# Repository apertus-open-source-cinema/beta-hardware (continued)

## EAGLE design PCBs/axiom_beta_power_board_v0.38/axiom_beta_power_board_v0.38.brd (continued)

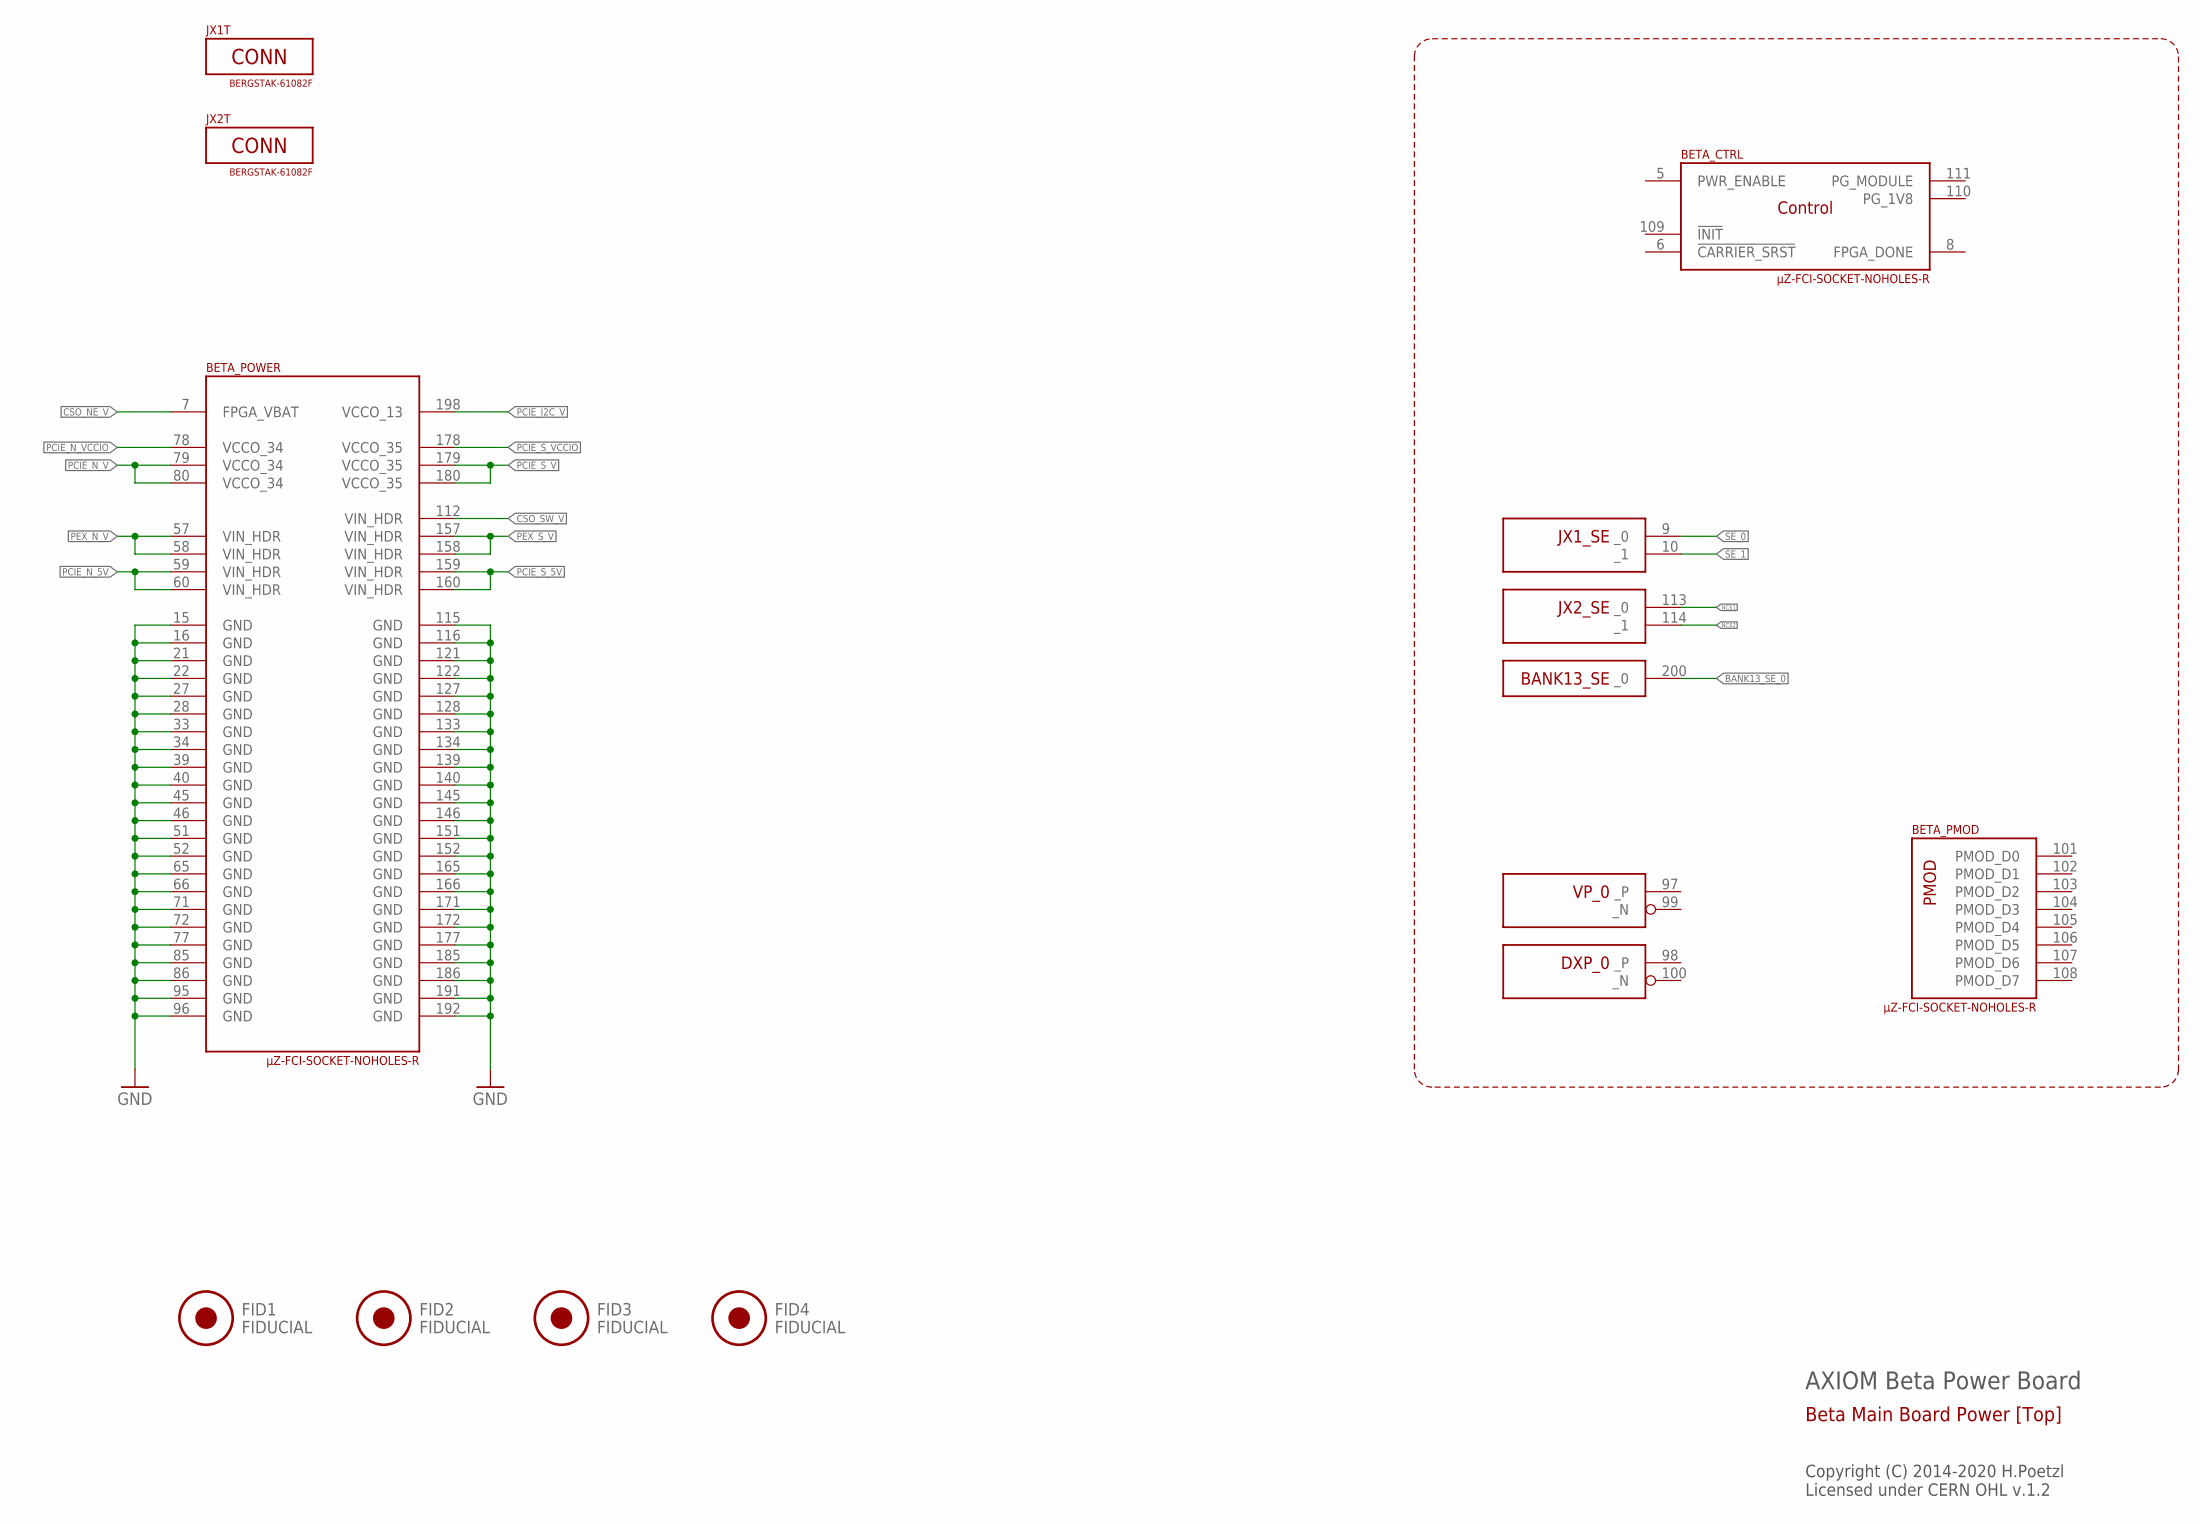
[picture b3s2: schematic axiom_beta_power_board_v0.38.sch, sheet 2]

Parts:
BETA: µZ-FCI-SOCKET-NOHOLES-R; µZ-SOCKET-NOHOLES-R
FID1, FID2, FID3, FID4: FIDUCIAL; FID_ARROW
JX1T, JX2T: BERGSTAK-61082F; 61082-FAKE

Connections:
BANK13_SE_0: BETA.200 (_0); also elsewhere on the board
CSO_NE_V: BETA.7 (FPGA_VBAT); also elsewhere on the board
CSO_SW_V: BETA.112 (VIN_HDR); also elsewhere on the board
GND: BETA.15 (GND), BETA.16 (GND), BETA.21 (GND), BETA.22 (GND), BETA.27 (GND), BETA.28 (GND), BETA.33 (GND), BETA.34 (GND), BETA.39 (GND), BETA.40 (GND), BETA.45 (GND), BETA.46 (GND), BETA.51 (GND), BETA.52 (GND), BETA.65 (GND), BETA.66 (GND), BETA.71 (GND), BETA.72 (GND), BETA.77 (GND), BETA.85 (GND), BETA.86 (GND), BETA.95 (GND), BETA.96 (GND), BETA.115 (GND), BETA.116 (GND), BETA.121 (GND), BETA.122 (GND), BETA.127 (GND), BETA.128 (GND), BETA.133 (GND), BETA.134 (GND), BETA.139 (GND), BETA.140 (GND), BETA.145 (GND), BETA.146 (GND), BETA.151 (GND), BETA.152 (GND), BETA.165 (GND), BETA.166 (GND), BETA.171 (GND), BETA.172 (GND), BETA.177 (GND), BETA.185 (GND), BETA.186 (GND), BETA.191 (GND), BETA.192 (GND); also elsewhere on the board
NC$1: BETA.113 (_0)
NC$2: BETA.114 (_1)
PCIE_I2C_V: BETA.198 (VCCO_13)
PCIE_N_5V: BETA.59 (VIN_HDR), BETA.60 (VIN_HDR)
PCIE_N_V: BETA.79 (VCCO_34), BETA.80 (VCCO_34); also elsewhere on the board
PCIE_N_VCCIO: BETA.78 (VCCO_34)
PCIE_S_5V: BETA.159 (VIN_HDR), BETA.160 (VIN_HDR)
PCIE_S_V: BETA.179 (VCCO_35), BETA.180 (VCCO_35); also elsewhere on the board
PCIE_S_VCCIO: BETA.178 (VCCO_35)
PEX_N_V: BETA.57 (VIN_HDR), BETA.58 (VIN_HDR)
PEX_S_V: BETA.157 (VIN_HDR), BETA.158 (VIN_HDR)
SE_0: BETA.9 (_0); also elsewhere on the board
SE_1: BETA.10 (_1); also elsewhere on the board

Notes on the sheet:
AXIOM Beta Power Board
Copyright (C) 2014-2020 H.Poetzl Licensed under CERN OHL v.1.2
Beta Main Board Power [Top]

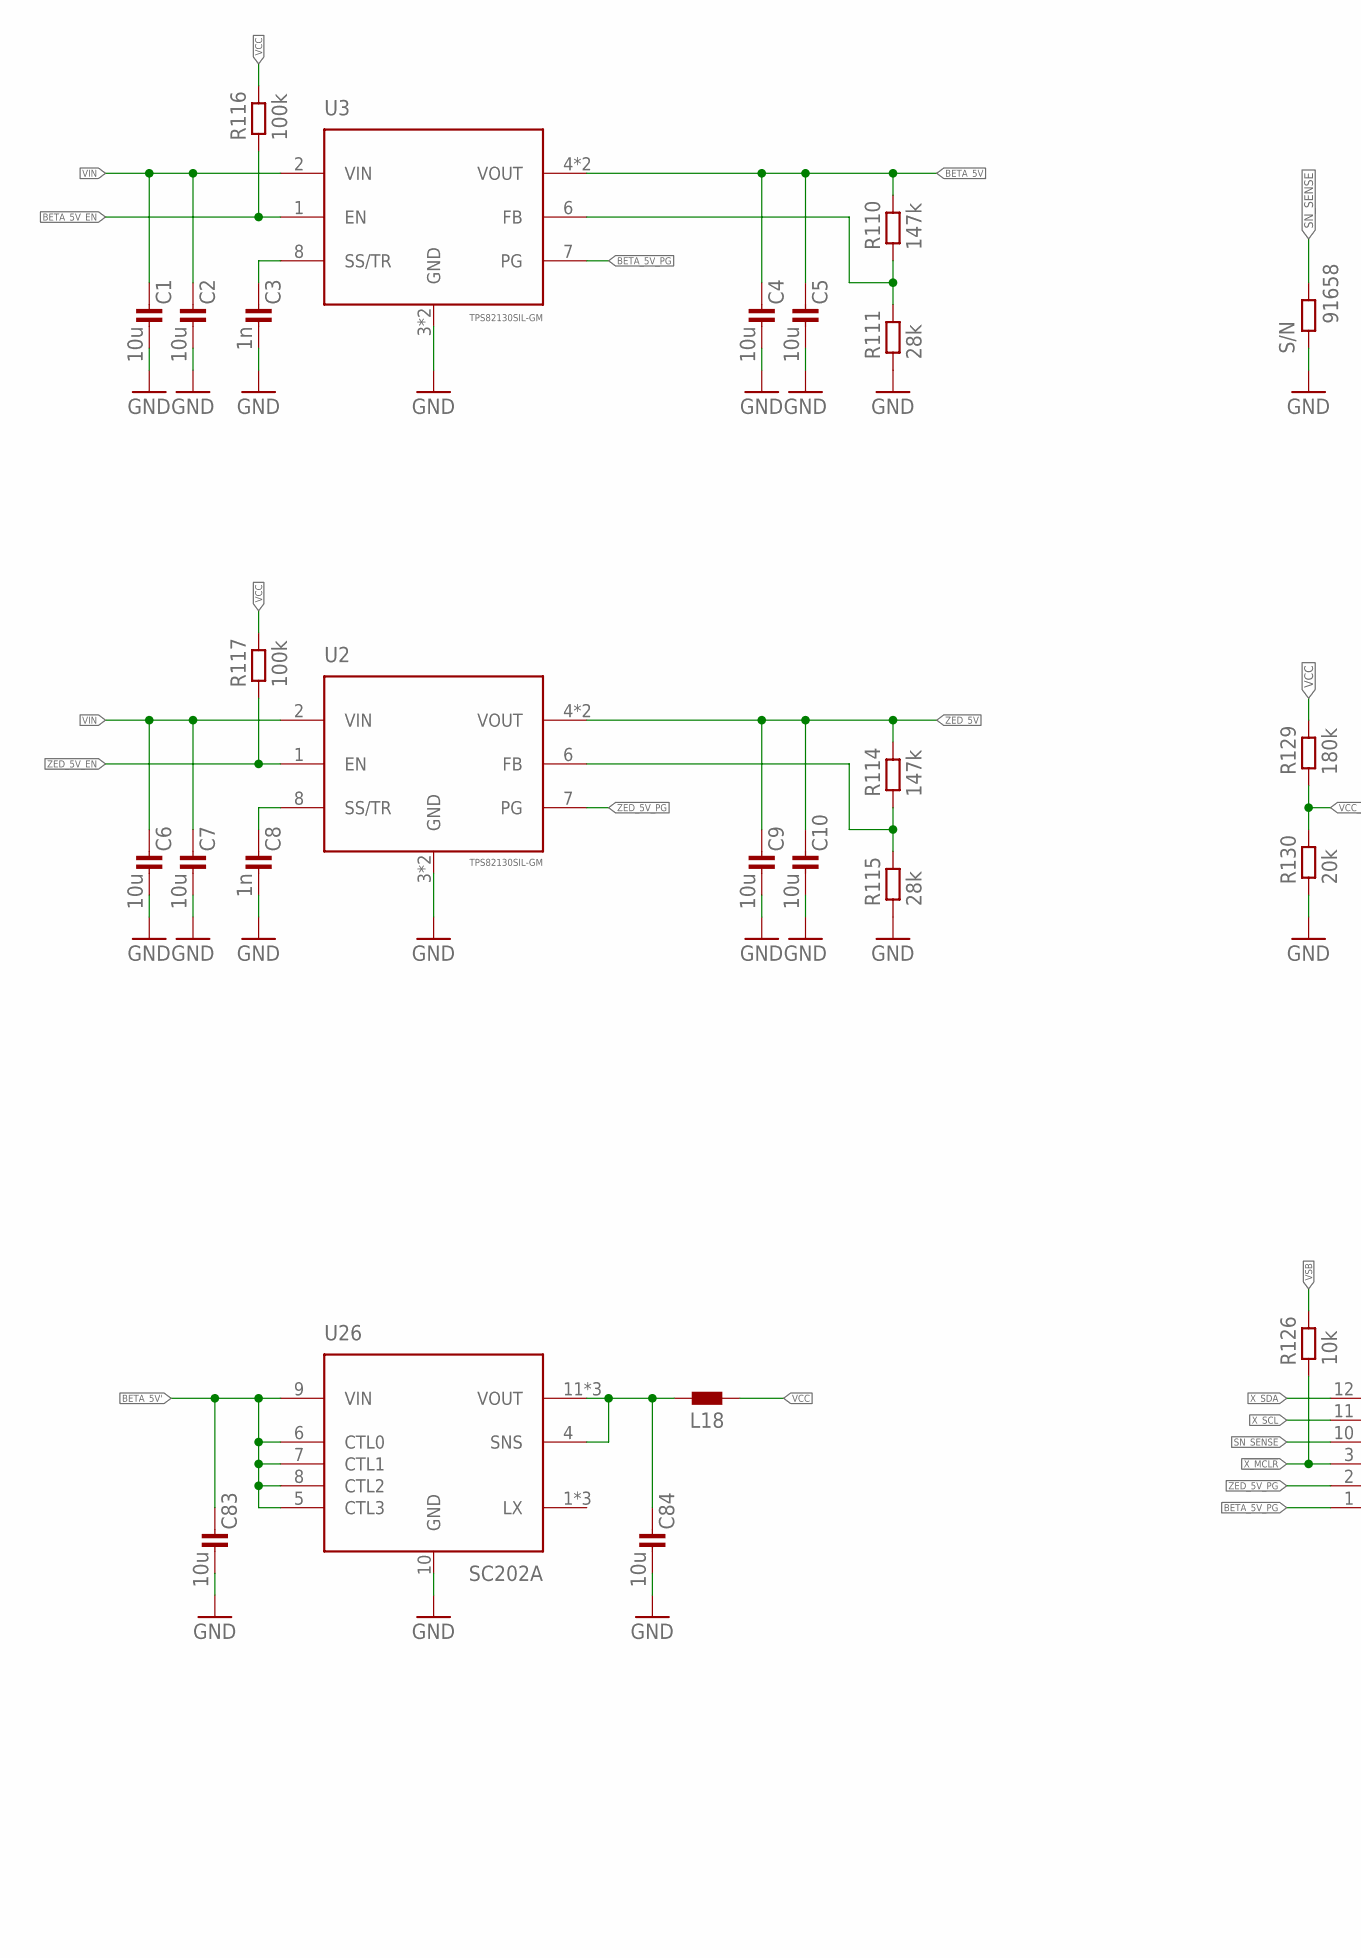
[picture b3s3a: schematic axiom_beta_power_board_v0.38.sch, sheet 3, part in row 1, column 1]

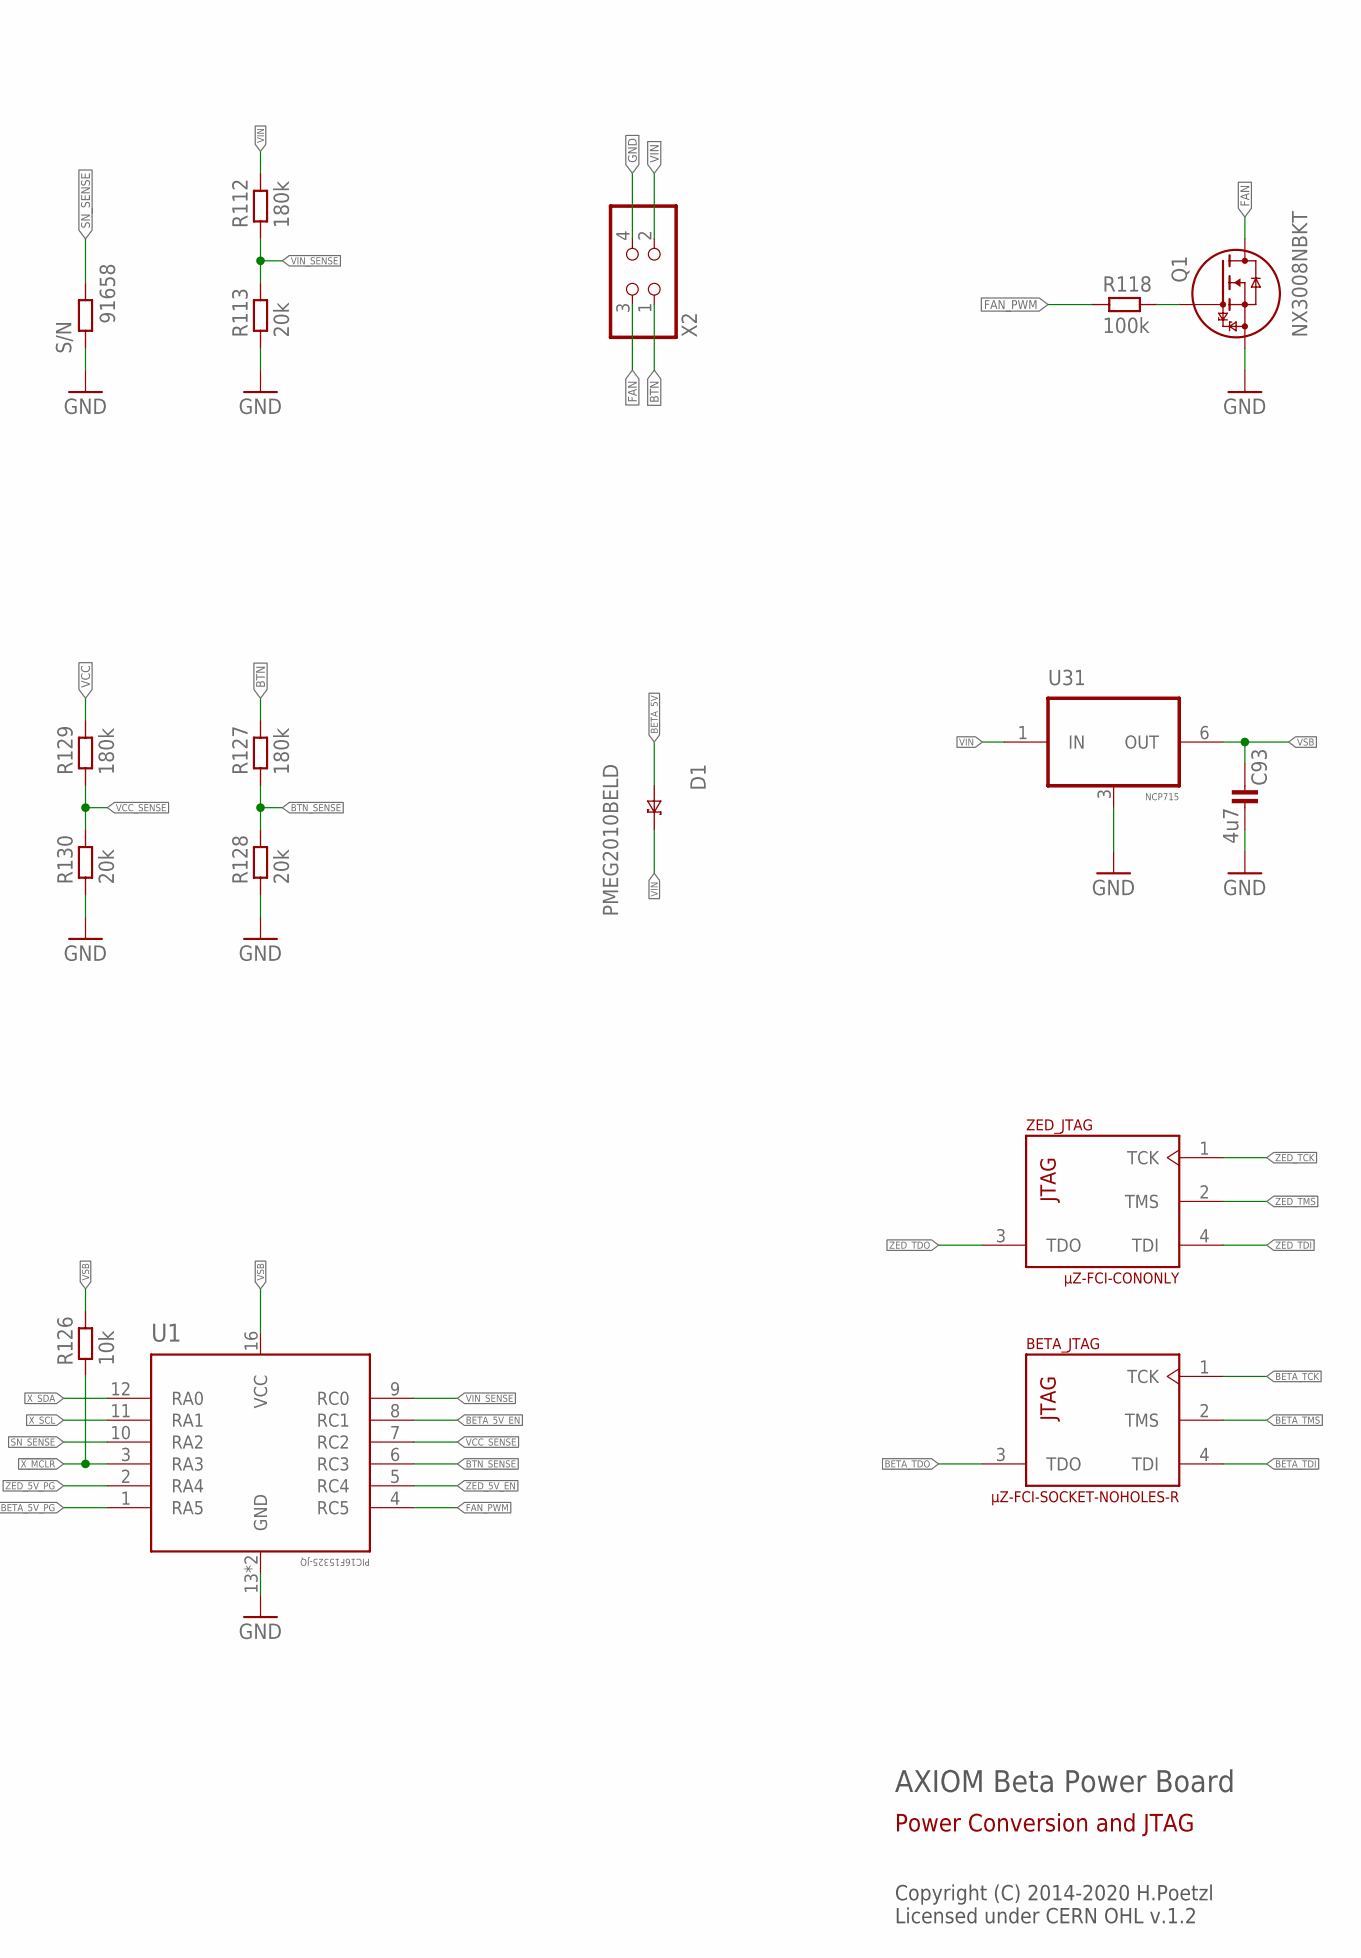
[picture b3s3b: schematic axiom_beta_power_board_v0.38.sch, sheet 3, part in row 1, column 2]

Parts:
BETA: µZ-FCI-SOCKET-NOHOLES-R; µZ-SOCKET-NOHOLES-R
C1, C5, C6, C10: 10u; 0603-B
C2, C4, C7, C9: 10u; 1206-C
C3, C8: 1n; 0402-C
C83, C84: 10u; 0603-C
C93: 4u7; 0402-B
D1: PMEG2010BELD; DFN1006D-2
L18: L0603-C; 0603-C
Q1: NX3008NBKT; SOT416
R110, R114: 147k; 0402-C
R111, R115: 28k; 0402-C
R112: 180k; 0402-B
R113: 20k; 0402-B
R116, R117: 100k; 0402-B
R118: 100k; 0402-C
R126: 10k; 0402-B
R127, R129: 180k; 0402-C
R128, R130: 20k; 0402-C
S/N: 91658; 3X2MM
U1: PIC16F15325-JQ; UQFN65P400X400X100-17N
U2, U3: TPS82130SIL-GM; SIL0008D-GM
U26: SC202A; MLPQ-13
U31: NCP715; DFN150X150X50-6N
X2: PINHD-2X02_2.54-90°; 2X02/90
ZED: µZ-FCI-CONONLY; µZ-CONONLY

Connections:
!X_MCLR: R126.2, U1.3 (RA3); also elsewhere on the board
BETA_5V: C4.1, C5.1, D1.A, R110.1, U3.4 (VOUT), U3.5 (VOUT); also elsewhere on the board
BETA_5V': C83.1, U26.5 (CTL3), U26.6 (CTL0), U26.7 (CTL1), U26.8 (CTL2), U26.9 (VIN); also elsewhere on the board
BETA_5V_EN: R116.2, U1.8 (RC1), U3.1 (EN)
BETA_5V_PG: U1.1 (RA5), U3.7 (PG)
BETA_TCK: BETA.1 (TCK)
BETA_TDI: BETA.4 (TDI)
BETA_TDO: BETA.3 (TDO)
BETA_TMS: BETA.2 (TMS)
BTN: R127.1, X2.1
BTN_SENSE: R127.2, R128.1, U1.6 (RC3)
FAN: Q1.3 (D), X2.3
FAN_PWM: R118.2, U1.4 (RC5)
GND: C1.2, C2.2, C3.2, C4.2, C5.2, C6.2, C7.2, C8.2, C9.2, C10.2, C83.2, C84.2, C93.2, Q1.2 (S), R111.2, R113.2, R115.2, R128.2, R130.2, S/N.1, U1.13 (GND), U1.EP (GND), U2.3 (GND), U2.EPAD (GND), U3.3 (GND), U3.EPAD (GND), U26.10 (GND), U31.3 (GND), X2.4; also elsewhere on the board
unnamed: C8.1, U2.8 (SS/TR)
unnamed: C3.1, U3.8 (SS/TR)
unnamed: Q1.1 (G), R118.1
unnamed: R110.2, R111.1, U3.6 (FB)
unnamed: R114.2, R115.1, U2.6 (FB)
REGOUT: C84.1, L18.1, U26.4 (SNS), U26.11 (VOUT), U26.12 (VOUT), U26.13 (VOUT)
SN_SENSE: S/N.2, U1.10 (RA2)
VCC: L18.2, R116.1, R117.1, R129.1; also elsewhere on the board
VCC_SENSE: R129.2, R130.1, U1.7 (RC2)
VIN: C1.1, C2.1, C6.1, C7.1, D1.C (K), R112.1, U2.2 (VIN), U3.2 (VIN), U31.1 (IN), X2.2
VIN_SENSE: R112.2, R113.1, U1.9 (RC0)
VSB: C93.1, R126.1, U1.16 (VCC), U31.6 (OUT); also elsewhere on the board
X_SCL: U1.11 (RA1); also elsewhere on the board
X_SDA: U1.12 (RA0); also elsewhere on the board
ZED_5V: C9.1, C10.1, R114.1, U2.4 (VOUT), U2.5 (VOUT); also elsewhere on the board
ZED_5V_EN: R117.2, U1.5 (RC4), U2.1 (EN)
ZED_5V_PG: U1.2 (RA4), U2.7 (PG)
ZED_TCK: ZED.1 (TCK)
ZED_TDI: ZED.4 (TDI)
ZED_TDO: ZED.3 (TDO)
ZED_TMS: ZED.2 (TMS)

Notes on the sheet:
AXIOM Beta Power Board
Copyright (C) 2014-2020 H.Poetzl Licensed under CERN OHL v.1.2
Power Conversion and JTAG

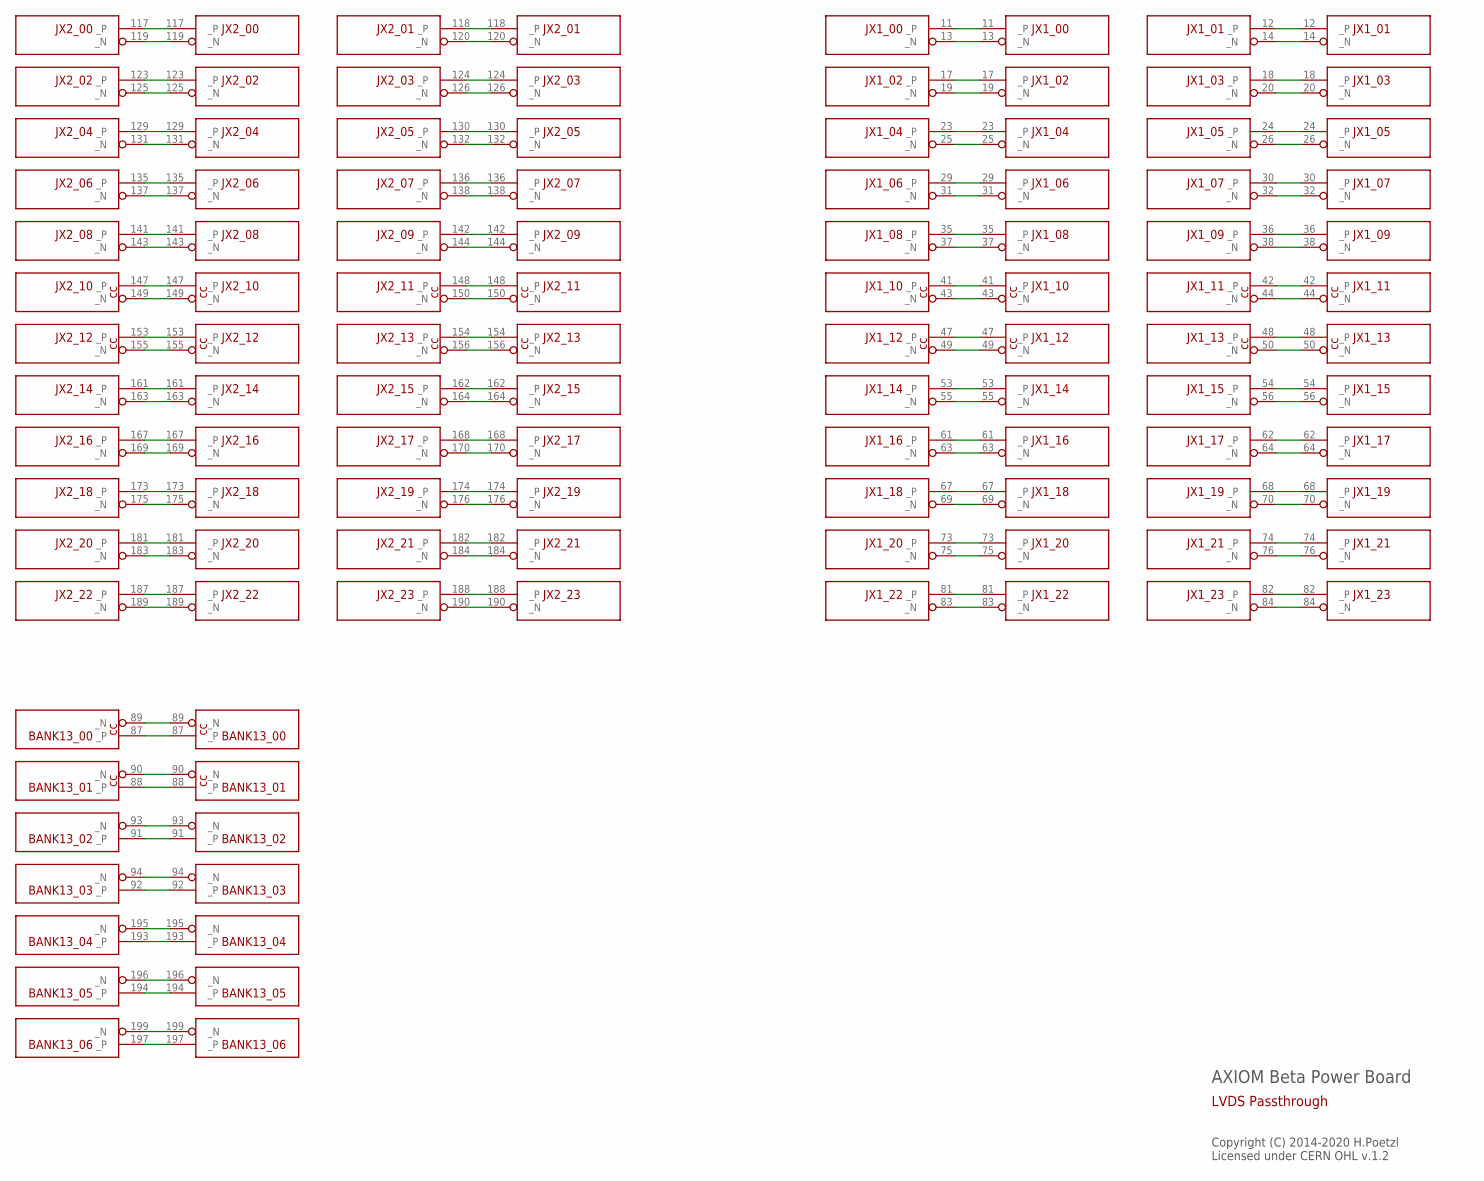
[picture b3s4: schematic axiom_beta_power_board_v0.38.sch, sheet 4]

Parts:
BETA: µZ-FCI-SOCKET-NOHOLES-R; µZ-SOCKET-NOHOLES-R
ZED: µZ-FCI-CONONLY; µZ-CONONLY

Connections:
BANK13_00_N: BETA.89 (_N), ZED.89 (_N)
BANK13_00_P: BETA.87 (_P), ZED.87 (_P)
BANK13_01_N: BETA.90 (_N), ZED.90 (_N)
BANK13_01_P: BETA.88 (_P), ZED.88 (_P)
BANK13_02_N: BETA.93 (_N), ZED.93 (_N)
BANK13_02_P: BETA.91 (_P), ZED.91 (_P)
BANK13_03_N: BETA.94 (_N), ZED.94 (_N)
BANK13_03_P: BETA.92 (_P), ZED.92 (_P)
BANK13_04_N: BETA.195 (_N), ZED.195 (_N)
BANK13_04_P: BETA.193 (_P), ZED.193 (_P)
BANK13_05_N: BETA.196 (_N), ZED.196 (_N)
BANK13_05_P: BETA.194 (_P), ZED.194 (_P)
BANK13_06_N: BETA.199 (_N), ZED.199 (_N)
BANK13_06_P: BETA.197 (_P), ZED.197 (_P)
JX1_00_N: BETA.13 (_N), ZED.13 (_N)
JX1_00_P: BETA.11 (_P), ZED.11 (_P)
JX1_01_N: BETA.14 (_N), ZED.14 (_N)
JX1_01_P: BETA.12 (_P), ZED.12 (_P)
JX1_02_N: BETA.19 (_N), ZED.19 (_N)
JX1_02_P: BETA.17 (_P), ZED.17 (_P)
JX1_03_N: BETA.20 (_N), ZED.20 (_N)
JX1_03_P: BETA.18 (_P), ZED.18 (_P)
JX1_04_N: BETA.25 (_N), ZED.25 (_N)
JX1_04_P: BETA.23 (_P), ZED.23 (_P)
JX1_05_N: BETA.26 (_N), ZED.26 (_N)
JX1_05_P: BETA.24 (_P), ZED.24 (_P)
JX1_06_N: BETA.31 (_N), ZED.31 (_N)
JX1_06_P: BETA.29 (_P), ZED.29 (_P)
JX1_07_N: BETA.32 (_N), ZED.32 (_N)
JX1_07_P: BETA.30 (_P), ZED.30 (_P)
JX1_08_N: BETA.37 (_N), ZED.37 (_N)
JX1_08_P: BETA.35 (_P), ZED.35 (_P)
JX1_09_N: BETA.38 (_N), ZED.38 (_N)
JX1_09_P: BETA.36 (_P), ZED.36 (_P)
JX1_10_N: BETA.43 (_N), ZED.43 (_N)
JX1_10_P: BETA.41 (_P), ZED.41 (_P)
JX1_11_N: BETA.44 (_N), ZED.44 (_N)
JX1_11_P: BETA.42 (_P), ZED.42 (_P)
JX1_12_N: BETA.49 (_N), ZED.49 (_N)
JX1_12_P: BETA.47 (_P), ZED.47 (_P)
JX1_13_N: BETA.50 (_N), ZED.50 (_N)
JX1_13_P: BETA.48 (_P), ZED.48 (_P)
JX1_14_N: BETA.55 (_N), ZED.55 (_N)
JX1_14_P: BETA.53 (_P), ZED.53 (_P)
JX1_15_N: BETA.56 (_N), ZED.56 (_N)
JX1_15_P: BETA.54 (_P), ZED.54 (_P)
JX1_16_N: BETA.63 (_N), ZED.63 (_N)
JX1_16_P: BETA.61 (_P), ZED.61 (_P)
JX1_17_N: BETA.64 (_N), ZED.64 (_N)
JX1_17_P: BETA.62 (_P), ZED.62 (_P)
JX1_18_N: BETA.69 (_N), ZED.69 (_N)
JX1_18_P: BETA.67 (_P), ZED.67 (_P)
JX1_19_N: BETA.70 (_N), ZED.70 (_N)
JX1_19_P: BETA.68 (_P), ZED.68 (_P)
JX1_20_N: BETA.75 (_N), ZED.75 (_N)
JX1_20_P: BETA.73 (_P), ZED.73 (_P)
JX1_21_N: BETA.76 (_N), ZED.76 (_N)
JX1_21_P: BETA.74 (_P), ZED.74 (_P)
JX1_22_N: BETA.83 (_N), ZED.83 (_N)
JX1_22_P: BETA.81 (_P), ZED.81 (_P)
JX1_23_N: BETA.84 (_N), ZED.84 (_N)
JX1_23_P: BETA.82 (_P), ZED.82 (_P)
JX2_00_N: BETA.119 (_N), ZED.119 (_N)
JX2_00_P: BETA.117 (_P), ZED.117 (_P)
JX2_01_N: BETA.120 (_N), ZED.120 (_N)
JX2_01_P: BETA.118 (_P), ZED.118 (_P)
JX2_02_N: BETA.125 (_N), ZED.125 (_N)
JX2_02_P: BETA.123 (_P), ZED.123 (_P)
JX2_03_N: BETA.126 (_N), ZED.126 (_N)
JX2_03_P: BETA.124 (_P), ZED.124 (_P)
JX2_04_N: BETA.131 (_N), ZED.131 (_N)
JX2_04_P: BETA.129 (_P), ZED.129 (_P)
JX2_05_N: BETA.132 (_N), ZED.132 (_N)
JX2_05_P: BETA.130 (_P), ZED.130 (_P)
JX2_06_N: BETA.137 (_N), ZED.137 (_N)
JX2_06_P: BETA.135 (_P), ZED.135 (_P)
JX2_07_N: BETA.138 (_N), ZED.138 (_N)
JX2_07_P: BETA.136 (_P), ZED.136 (_P)
JX2_08_N: BETA.143 (_N), ZED.143 (_N)
JX2_08_P: BETA.141 (_P), ZED.141 (_P)
JX2_09_N: BETA.144 (_N), ZED.144 (_N)
JX2_09_P: BETA.142 (_P), ZED.142 (_P)
JX2_10_N: BETA.149 (_N), ZED.149 (_N)
JX2_10_P: BETA.147 (_P), ZED.147 (_P)
JX2_11_N: BETA.150 (_N), ZED.150 (_N)
JX2_11_P: BETA.148 (_P), ZED.148 (_P)
JX2_12_N: BETA.155 (_N), ZED.155 (_N)
JX2_12_P: BETA.153 (_P), ZED.153 (_P)
JX2_13_N: BETA.156 (_N), ZED.156 (_N)
JX2_13_P: BETA.154 (_P), ZED.154 (_P)
JX2_14_N: BETA.163 (_N), ZED.163 (_N)
JX2_14_P: BETA.161 (_P), ZED.161 (_P)
JX2_15_N: BETA.164 (_N), ZED.164 (_N)
JX2_15_P: BETA.162 (_P), ZED.162 (_P)
JX2_16_N: BETA.169 (_N), ZED.169 (_N)
JX2_16_P: BETA.167 (_P), ZED.167 (_P)
JX2_17_N: BETA.170 (_N), ZED.170 (_N)
JX2_17_P: BETA.168 (_P), ZED.168 (_P)
JX2_18_N: BETA.175 (_N), ZED.175 (_N)
JX2_18_P: BETA.173 (_P), ZED.173 (_P)
JX2_19_N: BETA.176 (_N), ZED.176 (_N)
JX2_19_P: BETA.174 (_P), ZED.174 (_P)
JX2_20_N: BETA.183 (_N), ZED.183 (_N)
JX2_20_P: BETA.181 (_P), ZED.181 (_P)
JX2_21_N: BETA.184 (_N), ZED.184 (_N)
JX2_21_P: BETA.182 (_P), ZED.182 (_P)
JX2_22_N: BETA.189 (_N), ZED.189 (_N)
JX2_22_P: BETA.187 (_P), ZED.187 (_P)
JX2_23_N: BETA.190 (_N), ZED.190 (_N)
JX2_23_P: BETA.188 (_P), ZED.188 (_P)

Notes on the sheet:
AXIOM Beta Power Board
Copyright (C) 2014-2020 H.Poetzl Licensed under CERN OHL v.1.2
LVDS Passthrough

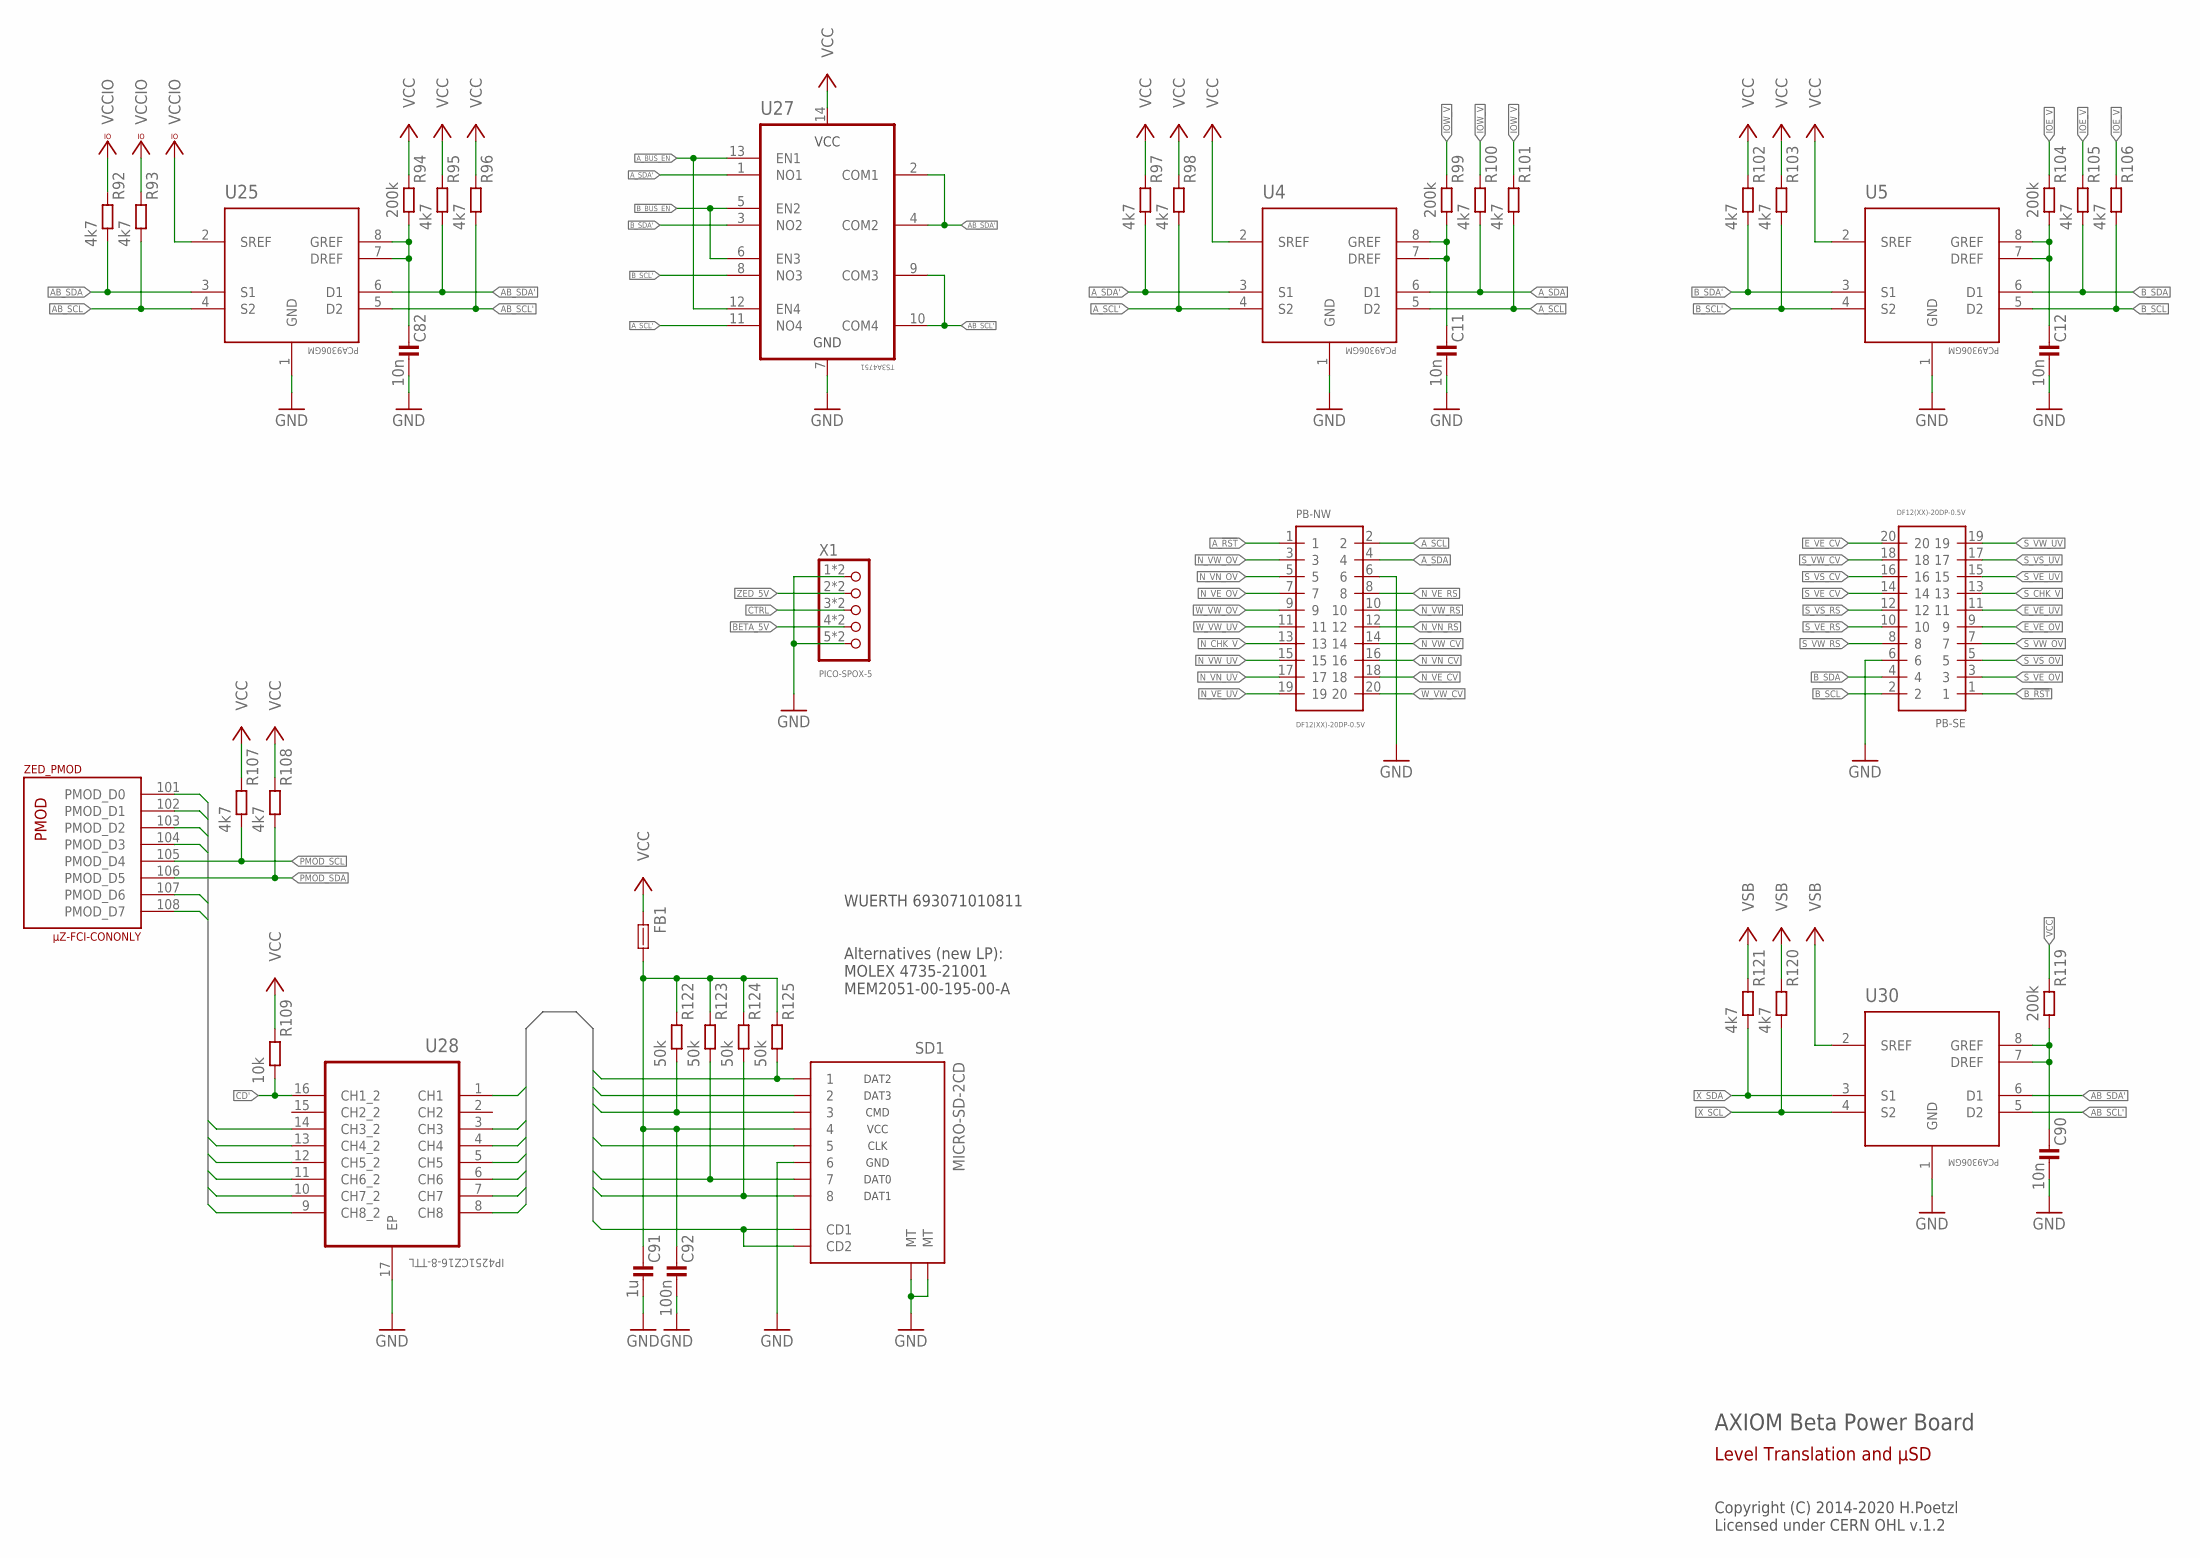
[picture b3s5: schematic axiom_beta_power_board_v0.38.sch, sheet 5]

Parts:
C11, C12, C82, C90: 10n; 0402-B
C91: 1u; 0402-B
C92: 100n; 0402-B
FB1: FB0402-B; 0402-B
PB-NW: DF12(XX)-20DP-0.5V
PB-SE: DF12(XX)-20DP-0.5V
R92, R93, R95, R96, R97, R98, R100, R101, R102, R103, R105, R106, R107, R108, R120, R121: 4k7; 0402-B
R94, R99, R104, R119: 200k; 0402-B
R109: 10k; 0402-B
R122, R123, R124, R125: 50k; 0402-B
SD1: MICRO-SD-2CD; TF-MICRO-SD_PP2
U4, U5, U25, U30: PCA9306GM; PCA9570GMH
U27: TS3A4751; SOP65P640X120-14N
U28: IP4251CZ16-8-TTL; SON40P135X330X55-17N
X1: PICO-SPOX-5
ZED: µZ-FCI-CONONLY; µZ-CONONLY

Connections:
AB_SCL: R93.2, U25.4 (S2); also elsewhere on the board
AB_SCL': R96.2, U25.5 (D2), U27.9 (COM3), U27.10 (COM4), U30.5 (D2)
AB_SDA: R92.2, U25.3 (S1); also elsewhere on the board
AB_SDA': R95.2, U25.6 (D1), U27.2 (COM1), U27.4 (COM2), U30.6 (D1)
A_!RST: PB-NW.1; also elsewhere on the board
A_BUS_EN: U27.12 (EN4), U27.13 (EN1); also elsewhere on the board
A_SCL: PB-NW.2, R101.2, U4.5 (D2)
A_SCL': R98.2, U4.4 (S2), U27.11 (NO4)
A_SDA: PB-NW.4, R100.2, U4.6 (D1)
A_SDA': R97.2, U4.3 (S1), U27.1 (NO1)
BETA_5V: X1.4, X1.4A (4); also elsewhere on the board
B_!RST: PB-SE.1; also elsewhere on the board
B_BUS_EN: U27.5 (EN2), U27.6 (EN3); also elsewhere on the board
B_SCL: PB-SE.2, R106.2, U5.5 (D2)
B_SCL': R103.2, U5.4 (S2), U27.8 (NO3)
B_SDA: PB-SE.4, R105.2, U5.6 (D1)
B_SDA': R102.2, U5.3 (S1), U27.3 (NO2)
CD: SD1.CD1, SD1.CD2, U28.1 (CH1)
CD': R109.2, U28.16 (CH1_2); also elsewhere on the board
CLK: SD1.5, U28.6 (CH6)
CMD: R122.2, SD1.3, U28.5 (CH5)
CTRL: X1.3, X1.3A (3)
DAT0: R123.2, SD1.7, U28.7 (CH7)
DAT1: R124.2, SD1.8, U28.8 (CH8)
DAT2: R125.2, SD1.1, U28.3 (CH3)
DAT3: SD1.2, U28.4 (CH4)
E_VE_CV: PB-SE.20
E_VE_OV: PB-SE.9
E_VE_UV: PB-SE.11
GND: C11.2, C12.2, C82.2, C90.2, C91.2, C92.2, PB-NW.6, PB-SE.6, SD1.6, SD1.MT1 (MT), SD1.MT2 (MT), U4.1 (GND), U5.1 (GND), U25.1 (GND), U27.7 (GND), U28.17 (EP), U30.1 (GND), X1.1, X1.1A (1), X1.5, X1.5A (5); also elsewhere on the board
IOE_V: R104.1, R105.1, R106.1; also elsewhere on the board
IOW_V: R99.1, R100.1, R101.1; also elsewhere on the board
unnamed: C91.1, C92.1, FB1.2, R122.1, R123.1, R124.1, R125.1, SD1.4
unnamed: C90.1, R119.2, U30.7 (DREF), U30.8 (GREF)
unnamed: C11.1, R99.2, U4.7 (DREF), U4.8 (GREF)
unnamed: C12.1, R104.2, U5.7 (DREF), U5.8 (GREF)
unnamed: C82.1, R94.2, U25.7 (DREF), U25.8 (GREF)
N_CHK_V: PB-NW.13
N_VE_CV: PB-NW.18
N_VE_OV: PB-NW.7
N_VE_RS: PB-NW.8
N_VE_UV: PB-NW.19
N_VN_CV: PB-NW.16
N_VN_OV: PB-NW.5
N_VN_RS: PB-NW.12
N_VN_UV: PB-NW.17
N_VW_CV: PB-NW.14
N_VW_OV: PB-NW.3
N_VW_RS: PB-NW.10
N_VW_UV: PB-NW.15
PMOD_D0: U28.9 (CH8_2), ZED.101 (PMOD_D0)
PMOD_D1: U28.10 (CH7_2), ZED.102 (PMOD_D1)
PMOD_D2: U28.12 (CH5_2), ZED.103 (PMOD_D2)
PMOD_D3: U28.11 (CH6_2), ZED.104 (PMOD_D3)
PMOD_D6: U28.14 (CH3_2), ZED.107 (PMOD_D6)
PMOD_D7: U28.13 (CH4_2), ZED.108 (PMOD_D7)
PMOD_SCL: R107.2, ZED.105 (PMOD_D4); also elsewhere on the board
PMOD_SDA: R108.2, ZED.106 (PMOD_D5); also elsewhere on the board
S_CHK_V: PB-SE.13
S_VE_CV: PB-SE.14
S_VE_OV: PB-SE.3
S_VE_RS: PB-SE.10
S_VE_UV: PB-SE.15
S_VS_CV: PB-SE.16
S_VS_OV: PB-SE.5
S_VS_RS: PB-SE.12
S_VS_UV: PB-SE.17
S_VW_CV: PB-SE.18
S_VW_OV: PB-SE.7
S_VW_RS: PB-SE.8
S_VW_UV: PB-SE.19
VCC: FB1.1, R94.1, R95.1, R96.1, R97.1, R98.1, R102.1, R103.1, R107.1, R108.1, R109.1, R119.1, U4.2 (SREF), U5.2 (SREF), U27.14 (VCC); also elsewhere on the board
VCCIO: R92.1, R93.1, U25.2 (SREF); also elsewhere on the board
VSB: R120.1, R121.1, U30.2 (SREF); also elsewhere on the board
W_VW_CV: PB-NW.20
W_VW_OV: PB-NW.9
W_VW_UV: PB-NW.11
X_SCL: R120.2, U30.4 (S2); also elsewhere on the board
X_SDA: R121.2, U30.3 (S1); also elsewhere on the board
ZED_5V: X1.2, X1.2A (2); also elsewhere on the board

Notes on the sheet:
AXIOM Beta Power Board
Copyright (C) 2014-2020 H.Poetzl Licensed under CERN OHL v.1.2
Level Translation and µSD
WUERTH 693071010811 Alternatives (new LP): MOLEX 4735-21001 MEM2051-00-195-00-A
